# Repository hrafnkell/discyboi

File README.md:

# discyboi

**[discyboi.com](https://discyboi.com)** · [flight lab](https://discyboi.com/lab/)

A flight tracker that mounts on a disc golf disc and reports each throw over Bluetooth. The goal is enough sensor data for reliable flight prediction:

- release detection and release speed
- hyzer angle and nose angle
- spin rate
- wobble / off-axis torque

The hardware is a small round PCB built around an nRF54L15 BLE SoC and IMUs read over SPI. It runs from a CR2032 coin cell and mounts in a small screw-on case under the flight plate, or can be sealed (potted or conformal-coated) into the disc.

## Hardware

The current board is **[v4](v4/)**: Ø34 mm, a Fanstel BC15M module (nRF54L15, PCB antenna), and 2 × LSM6DSV320X (one at the centre, one at r = 9 mm). It runs from a CR2032 in a clip on the back, through an MCP1700 3.0 V regulator. The LiPo charger is on the board but not fitted (LIR2032 option). Gerbers and BOMs are in `v4/jlcpcb/`.

Each LSM6DSV320X has a ±320 g high-g accelerometer next to the IMU, and placing one 9 mm off-centre means spin rate can be computed from centripetal acceleration well past the gyro's 4000 dps limit. See the [v4 README](v4/README.md) for specs, the full pinout and how to regenerate the board.

Earlier revisions (v1: bare nRF54L15 + ADXL375, v2: Holyiot module, v3: the v4 design with a LiPo) were removed from the tree; they are in the git history.

## Layout

```
datasheets/            LSM6DSV320X IMU datasheet, TE/Linx coin-cell clip drawings (003 = CR2032, used on v4)
v4/                    KiCad project for the current board
v4/gen/                Python generators for v4's schematic, footprints and PCB (source of truth)
v4/jlcpcb/             fabrication outputs (gerbers, BOM, CPL)
v4/enclosure/          OpenSCAD case (base + screw-on battery lid), STLs, centring jig
firmware/              Zephyr firmware for the v4 board
web/                   discyboi.com: landing page, and the three.js flight lab (simulator, Web Bluetooth client, throw history)
```

## Tools

- KiCad 9 (schematic, PCB, `kicad-cli` for ERC/DRC and exports)
- Freerouting (`~/Downloads/freerouting*.AppImage`) for autorouting v4
- JLCPCB for fabrication. Mouser for the parts (single-supplier BOM)

## Firmware

[`firmware/`](firmware/) holds the Zephyr (v4.0) application for the v4 board. It runs on hardware (both IMUs, motion detection) and takes updates over Bluetooth through MCUboot; real throws are still to be checked. Its analysis maths passes host tests.

- **Detection:** finds throws with a pull/release state machine at 960 Hz, keeping a 3 s ring buffer.
- **Measurements:** release speed, hyzer, nose and launch angles, spin (from the gyro, or centripetal when the gyro saturates), wobble and flight time.
- **BLE:** sends each result, plus the battery level, and can send the raw capture for offline analysis.
- **Build:** `firmware/build.sh` runs the build in Docker. Flashing is over SWD (Tag-Connect), with logs over RTT.

See the [firmware README](firmware/README.md) for the BLE protocol and the bring-up TODO list.

## Web

[`web/`](web/) is a browser app (Vite + TypeScript + three.js, run with bun). It simulates disc flights from speed, spin, hyzer, nose and launch angle plus a disc's flight numbers, and animates them in 3D. It receives throws from the disc over Web Bluetooth (or from a fake disc with `?fake=1`) and keeps a throw history. It runs at [discyboi.com](https://discyboi.com): a landing page at `/` and the app under `/lab/`. See the [web README](web/README.md).

## Licence

Open source and open hardware: CERN-OHL-S-2.0 for the hardware, GPL-3.0 for the firmware, AGPL-3.0 for the web app, and CC-BY-SA-4.0 for the photos. Build your own freely; if you share or sell something based on it, credit this project and publish your changes under the same licence. The name "discyboi" is not included. See [LICENSE.md](LICENSE.md).

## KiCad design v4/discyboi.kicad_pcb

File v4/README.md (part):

# discyboi v4

Round 34 mm flight-tracker board that sits on a disc golf disc. It has a Fanstel BC15M (nRF54L15) BLE module and two LSM6DSV320X IMUs, and runs from a **CR2032 coin cell** in a clip on the back of the board.

v4 is v3 (now only in the git history) with the LiPo replaced by a replaceable coin cell, because small LiPo cells are hard to get shipped. The electronics, pinout and firmware are otherwise the same. The LiPo charger stays on the board but is **not fitted** (DNP). Fit it only if you use a rechargeable LIR2032.

| Top | Bottom (seen from below) |
|---|---|
|  |  |

## Specs

| | |
|---|---|
| MCU / radio | Fanstel **BC15M**: nRF54L15, BLE, PCB trace antenna. 6.0 × 9.6 mm, 36-pad LGA (6×6, 0.9 mm pitch) |
| IMU (centre) | **LSM6DSV320X** (U5): ±4000 dps gyro, ±16 g low-g accel and ±320 g high-g accel |
| IMU 2 (off-centre) | **LSM6DSV320X** (U3) at r = 9 mm, same orientation as U5 |
| Sensor bus | SPI (SPIM00, port 2), shared SCK/MOSI/MISO, one CS per IMU, two interrupt lines per IMU |
| Battery | **CR2032** in a TE/Linx **BAT-HLD-003-SMT** clip (BT1) on the bottom side. The cell's negative face sits on a Ø14 mm pad; the clip is the + contact |
| Bulk capacitor | C22 100 µF (1206) on VBAT, which supplies the radio's transmit bursts so the coin cell doesn't sag |
| Charger (**DNP**) | MCP73831-2 (U4) with R7 = 47 k (~21 mA), D2, R8, C13, D3 and R9 are not fitted. Fit them only for a rechargeable **LIR2032**. **Never fit them with a CR2032 in the clip** |
| Regulator | MCP1700-3002E LDO → **3.0 V** rail (+3V0) for everything |
| Battery sense | VBAT → 10 M / 10 M divider (+100 nF) → P1.06 / AIN2, so the ADC reads VBAT/2 (≈0.2 µA drain; sample slowly) |
| Charger detect | R9 (DNP) / R10 100 k → P1.03 (CHG_DET, NFC pad used as GPIO). With R9 unfitted, R10 holds it low |
| Debug | Tag-Connect TC2030-IDC-NL (no legs): SWD + reset. Logging over RTT |
| Status | Green LED on P2.09 (active high, 1 k) |
| PCB | 4 layers, Ø34 mm circle with a straight flat 10.2 mm above centre for the antenna. Finish: lead-free **HASL** (free, long shelf life), ENIG (flattest, costs extra) or OSP (flat, but short shelf life). See Ordering |

### Why two IMUs

The gyro saturates at 4000 dps, which is about **667 rpm**, and discs spin faster than that. U3 sits 9 mm from the centre, so it sees centripetal acceleration a = ω²r. Subtracting U5's reading, which sits at the centre and sees linear and gravity components only, leaves the spin term:

| Range used | Max a | Max spin at r = 9 mm |
|---|---|---|
| Gyro | – | ~667 rpm |
| Low-g accel ±16 g | 157 m/s² | ~1260 rpm |
| High-g accel ±320 g | 3140 m/s² | ~5600 rpm |

U5 at the centre also gives orientation (hyzer, nose angle, wobble) and release and impact detection.

## Pinout

### BC15M module (U1)

Only perimeter pads are used, so every signal escapes on the top layer with no vias under the module. Interrupts are on P0/P1 (GPIOTE30 / GPIOTE20). The SPI lines are on SPIM00's dedicated port-2 pins.

| Pad | nRF54L15 pin | Net | Function |
|---|---|---|---|
| F6 | VDD | +3V0 | Supply (C1 10 µF + C2 100 nF) |
| E1, F1 | GND | GND | |
| A3 | SWDIO | SWDIO | Debug |
| A4 | SWDCLK | SWDCLK | Debug |
| F3 | nRESET | NRESET | Debug / reset |
| C6 | P2.01 | SPI_SCK | SPIM00 SCK |
| D6 | P2.02 | SPI_MOSI | SPIM00 SDO |
| F5 | P2.04 | SPI_MISO | SPIM00 SDI |
| F2 | P2.06 | IMU_CS | U5 (centre IMU) chip select |
| A6 | P2.05 | ACC_CS | U3 (r = 9 mm IMU) chip select |
| A2 | P0.00 | IMU_INT1 | U5 INT1 |
| B1 | P1.08 | IMU_INT2 | U5 INT2 |
| A1 | P0.01 | ACC_INT1 | U3 INT1 |
| D1 | P1.12 | ACC_INT2 | U3 INT2 |
| B6 | P1.06 / AIN2 | VBAT_SENSE | Battery voltage ÷ 2 |
| A5 | P2.09 | LED | Green status LED (D1) via R5 |
| F4 | P1.03 (NFC1) | CHG_DET | Charger present (VCHG ÷ 2). Configure the NFC pads as GPIO |

All other pads are not connected.

### LSM6DSV320X (U5 centre, U3 off-centre)

SPI 4-wire mode. The analog hub / Qvar inputs are tied to GND and the aux SPI pins are left open (datasheet table 2, mode 1).

| Pin | Name | U5 net | U3 net |
|---|---|---|---|
| 1 | SDO/SA0 | SPI_MISO | SPI_MISO |
| 2 | SDx | GND | GND |
| 3 | SCx | GND | GND |
| 4 | INT1 | IMU_INT1 | ACC_INT1 |
| 5 | VDDIO | +3V0 | +3V0 |
| 6, 7 | GND | GND | GND |
| 8 | VDD | +3V0 | +3V0 |
| 9 | INT2 | IMU_INT2 | ACC_INT2 |
| 10 | OCS_Aux | NC | NC |
| 11 | SDO_Aux | NC | NC |
| 12 | CS | IMU_CS | ACC_CS |
| 13 | SCL/SPC | SPI_SCK | SPI_SCK |
| 14 | SDA/SDI | SPI_MOSI | SPI_MOSI |

Decoupling: U5 has C10/C12 100 nF and C11 1 µF. U3 has C19/C20 100 nF and C21 1 µF.

### SWD: Tag-Connect TC2030 (J2)

| Pin | Signal |
|---|---|
| 1 | +3V0 (VTref) |
| 2 | SWDIO |
| 3 | NRESET |
| 4 | SWDCLK |
| 5 | GND |
| 6 | NC |

The footprint is the no-legs version, so use a TC2030-CTX-NL cable with the retaining clip. J2 sits at the top left so the cable's guide pins, which poke through the board, clear the coin cell on the back. Or solder thin wires to the pads for bring-up.

### Pads

| Pad | Net | |
|---|---|---|
| TP1 | VBAT | BAT+ (bench supply / measuring) |
| TP2 | GND | BAT− |
| TP3 | VCHG | CHG+ (5 V in, LIR2032 build only) |
| TP4 | GND | CHG− |

All four pads are 2 × 2 mm, along the bottom edge of the top side. With a CR2032 build, don't connect anything to CHG+.

## Power path

```
BT1 CR2032 (clip, bottom) ── VBAT ── C22 100 µF, C14 4.7 µF
                              │   └─ R3/R4 10M:10M ─► VBAT_SENSE (P1.06)
                              ▼
                     MCP1700 3.0 V (U2, C16 in / C17 out) ──► +3V0

(DNP, LIR2032 only)  CHG+ 5V ──D3──C13──► MCP73831 (U4, 21 mA) ──► VBAT
```

A fresh CR2032 is about 3.0 V, so the MCP1700 is in dropout and the rail simply follows the cell (≈2.6–3.0 V for most of its life). The nRF54L15 and both IMUs run down to about 1.7–1.8 V, so the cell can be used almost to empty.

**Runtime (estimate).** About 1.7–2 mA while armed (both IMUs at 960 Hz plus the CPU) and 11 µA in deep sleep. A CR2032 gives roughly 150–180 mAh at that load, so about 35–40 rounds of two hours armed time. Cold weather reduces this. The radio's 5–10 mA transmit bursts come mostly from C22.

**Battery level.** The firmware detects the battery type (`CONFIG_DISCY_BATTERY_AUTO`, default): coin-cell curve (3.0 V = 100 %, 2.0 V = 0 %) until VBAT is seen above 3.45 V, then the LiPo curve.

## LiPo build (same board)

The same board can run from a 1S LiPo instead of the coin cell, for example a 20 × 20 × 4.5 mm, 150 mAh pouch.

**Each board is either a coin-cell build or a LiPo build, never both.** A LiPo or a 5 V charger connected to a primary CR2032 forces current into it, and that can make the cell leak, swell or catch fire. On a LiPo board, leave the clip off.

| | Coin-cell build | LiPo build |
|---|---|---|
| BT1 clip | Fitted | **Not fitted** |
| Battery | CR2032 in the clip | LiPo leads: + to a clip tab pad (or TP1 BAT+), − to the round pad's edge (or TP2 BAT−) |
| U4, R8, D2, C13, D3, R9 | Not fitted | Fitted |
| R7 (charge current = 1000 V / R7) | Not fitted | **10 k = 100 mA** for 150 mAh (≈0.7C) |
| Charging | – | 5 V on CHG+ / CHG− (TP3 / TP4). The red LED is lit while charging |
| CHG_DET (P1.03) | Held low by R10 | High while a charger is connected |

Notes for the LiPo build:
- **Use a protected cell.** It needs a protection PCB on the tabs for over-discharge and short-circuit. Small pouch cells often have it, which makes them a couple of mm longer than the nominal size.
- **Insulate the cell from the board.** Put a layer of Kapton tape over the bottom of the board before you stick the cell there, so the pouch can't rub through to the exposed round pad or the vias.
- **Placement:** the 20 × 20 mm cell fits on the bottom in the same place as the coin cell, centred 2.5 mm below the board centre, so balance and antenna clearance stay the same.
- **Regulator:** the LDO now regulates properly to 3.0 V. Nothing else on the board changes.
- **Same firmware:** it switches to the LiPo battery curve on its own once VBAT is above 3.45 V.

## PCB

- **Stackup:** F.Cu signals plus GND pour, In1 solid GND, In2 solid +3V0, B.Cu GND pour. GND stitching vias run around the rim.
- **Rules:** 0.12 mm clearance. Tracks are 0.15 mm signal, 0.25 mm +3V0/GND and 0.3 mm VBAT/VCHG. Vias are 0.45 / 0.2 mm (JLC charges for a 4-wire Kelvin test on 0.4 / 0.2 mm vias), with 0.25 mm copper-to-edge clearance.
- **Antenna:** the module is placed so that its shield/antenna boundary sits on the board flat. The 3.6 mm trace antenna overhangs the edge with no copper under it. Vias are kept out from under the module.
- **Coin cell:** the cell centre is 2.5 mm below the board centre, which keeps it more than 2 mm from the antenna edge and partly balances the module at the top. The clip's open end faces the module and the cell slides in from that side.
  - The negative pad is Ø14 mm instead of the 17.9 mm in TE's drawing. A CR2032's flat negative face is wider than that, and the smaller pad leaves a ring of bottom-layer routing under the cell. Those traces stay under solder mask.
  - The pad has GND vias in it. That's fine for a pressure contact.
- **Mass:** the cell is about 3 g. Check the disc's balance with the cell fitted before potting or gluing.

## Ordering

- **JLCPCB (PCB):** upload `jlcpcb/discyboi-gerbers.zip`.
  - 4 layers, **1.0 mm** thick (the enclosure STLs assume 1.0 mm). Use a **0.10 mm** top-side stencil.
  - Surface finish:
    - **Lead-free HASL** (free) suits boards that may sit in a drawer, because it stays solderable for a year or more. The battery's negative pad comes solder-coated, so it needs no treatment unless it's visibly lumpy; then flatten it with the iron and solder wick. HASL pads are slightly domed, so take a little extra care with the 0.5 mm-pitch IMUs: use the 0.10 mm stencil, press each IMU down level after placing it, and inspect after reflow.
    - **ENIG** costs extra. It's the flattest finish and has a long shelf life. The battery pad needs nothing.
    - **OSP** (free) is flat, but assemble within a few months. Tin the battery pad after reflow (flux and solder, then wick it thin and flat), because bare copper oxidises.
  - Order a **top-side** stencil only, 0.10 mm thick.
  - The stencil also has apertures for the unfitted charger pads. The paste just tins those pads, which is harmless and handy if you fit the charger later.
- **JLC assembly (optional):** `jlcpcb/discyboi-BOM.csv` + `discyboi-CPL.csv` cover all fitted top-side parts, the BC15M included. Unfitted parts and the battery clip are left out.
  - **The BC15M, the LSM6DSV320X and the 10 M resistors have no LCSC code.** Get them through JLCPCB's Global Sourcing (from Mouser / DigiKey) or send them as consigned parts. The BC15M is an LGA: ask for X-ray inspection.
- **Generic passives:** the caps, resistors and LED can be any brand that meets the spec in the Mouser BOM's Substitute column (the MPNs are examples). Mind the 100 µF (6.3 V or more, X5R) and the LED (yellow-green AlInGaP, Vf ≈ 2 V: an InGaN "true green" barely lights from 3 V through 1 k). U1, U2, U3/U5 and BT1 must be the exact parts.
- **Mouser:** `discyboi-mouser-BOM.csv` lists every fitted part with its MPN, including the BC15M (Mouser 308-BC15M) and the BAT-HLD-003-SMT clip. Not in any BOM: the CR2032 itself, and for the case 3 × M2 × 6 mm countersunk screws and VHB tape.
  - For a rechargeable build, also buy U4 MCP73831T-2ACI/OT, R8 1 k, D2 (LTST-C191KRKT), C13 4.7 µF, D3 ESD5Z5.0T1G and R9 100 k.
  - R7 depends on the cell: 10 k (RC0402FR-0710KL, 100 mA) for a 150 mAh LiPo, or 47 k (RC0402FR-0747KL, 21 mA) for a LIR2032.
- **Assembly order:**
  1. Paste and reflow the top side (BC15M, IMUs and passives).
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
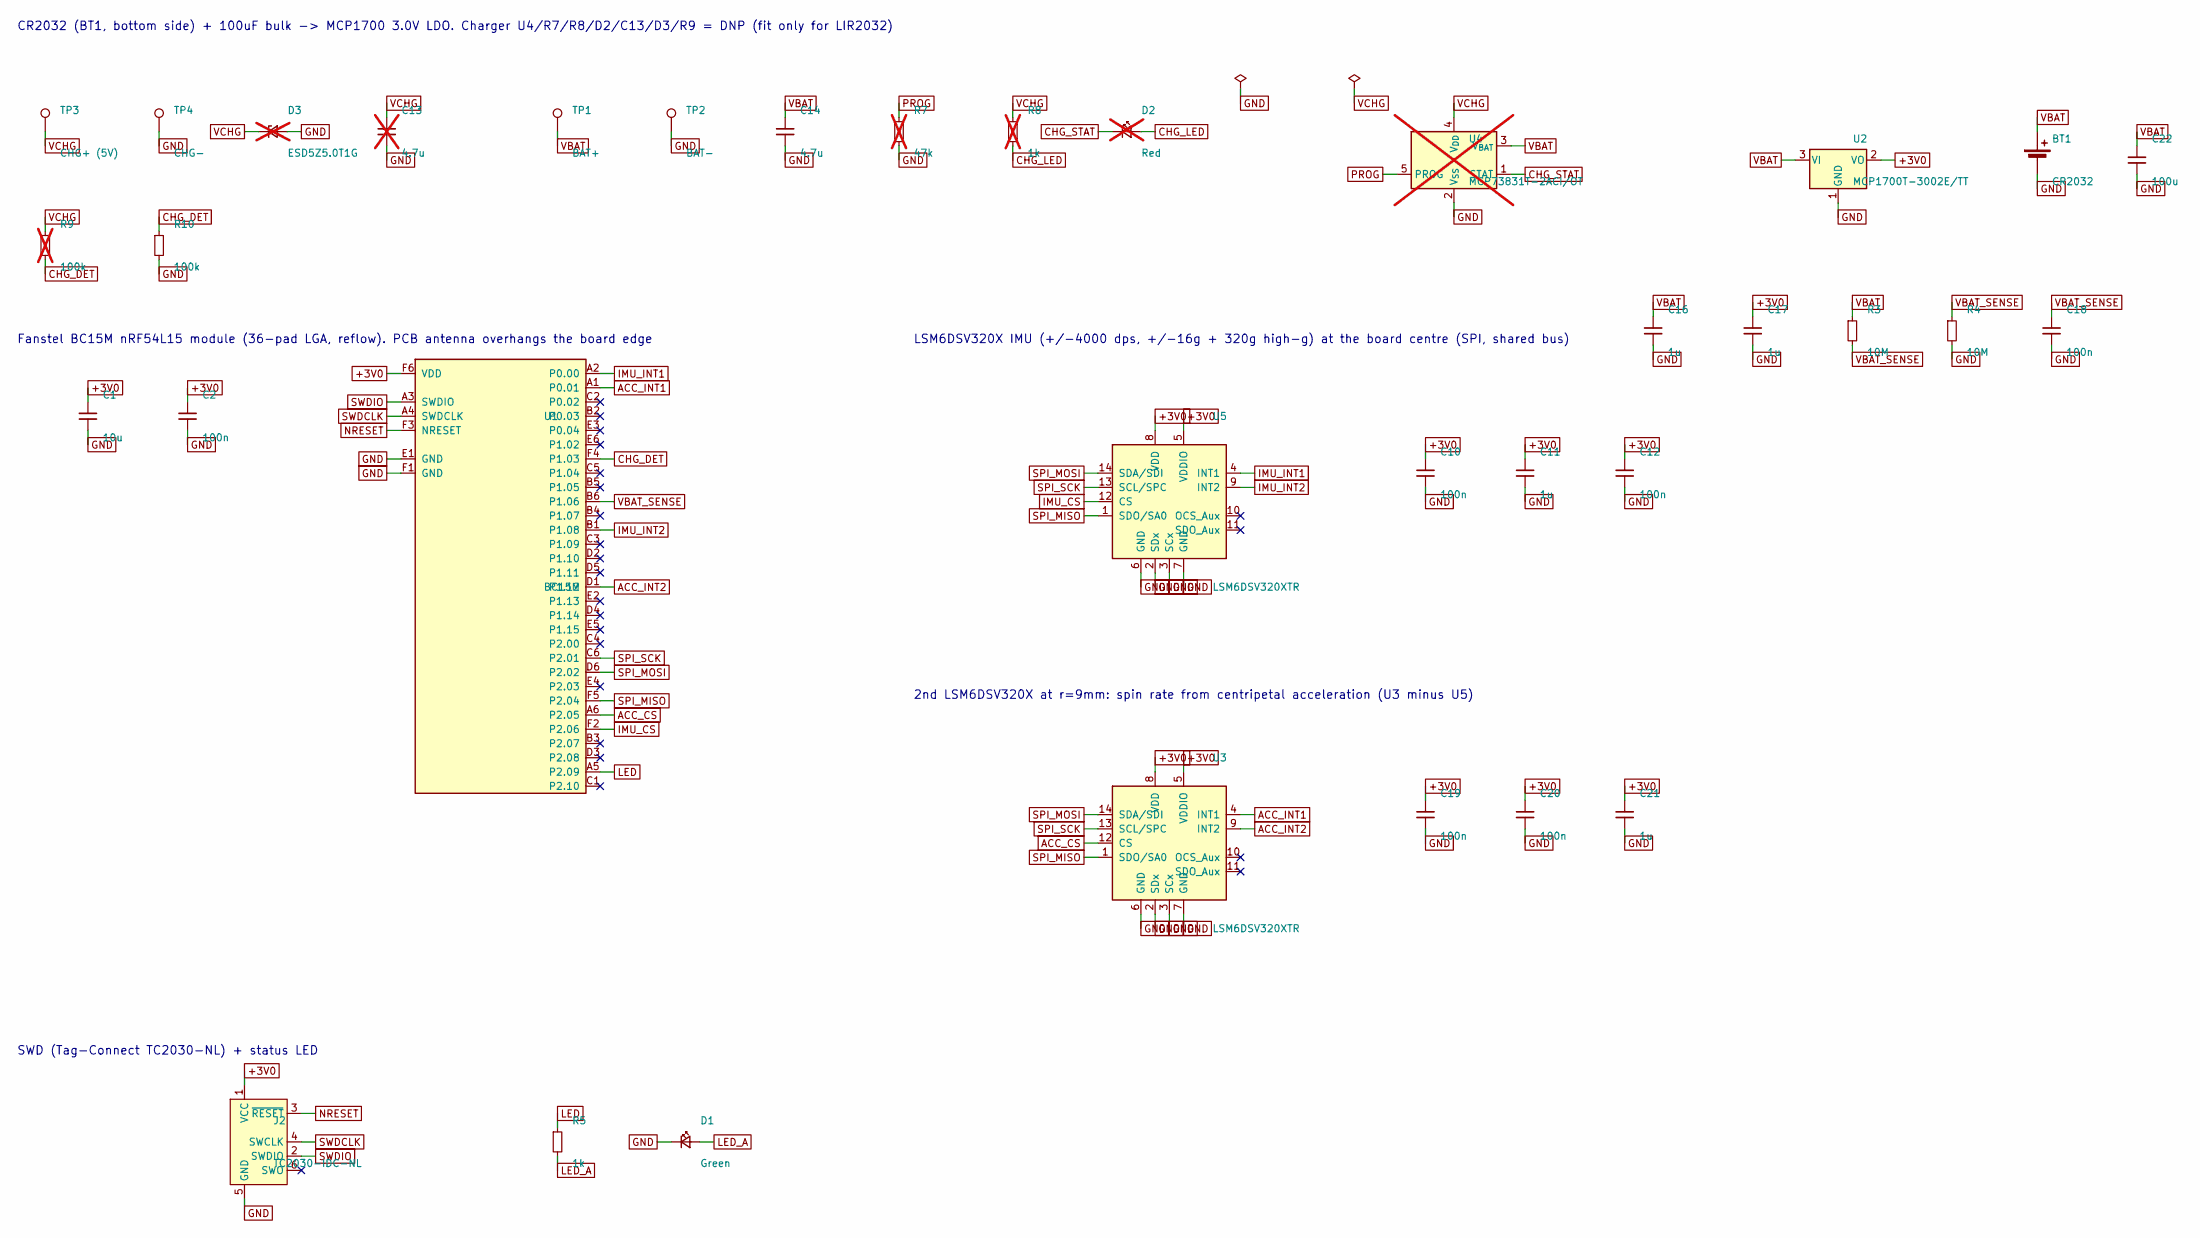
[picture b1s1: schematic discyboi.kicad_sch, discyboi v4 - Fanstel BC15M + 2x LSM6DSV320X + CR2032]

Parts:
BT1: CR2032; Linx_BAT-HLD-003-SMT; MPN BAT-HLD-003-SMT
C1: 10u; C_0402_1005Metric; MPN CL05A106MQ5NUNC; LCSC C15525
C2, C10, C12, C18, C19, C20: 100n; C_0402_1005Metric; MPN CL05B104KO5NNNC; LCSC C1525
C11, C16, C17, C21: 1u; C_0402_1005Metric; MPN CL05A105KA5NQNC; LCSC C52923
C13: 4.7u; C_0402_1005Metric; MPN CL05A475MP5NRNC; LCSC C23733; not fitted
C14: 4.7u; C_0402_1005Metric; MPN CL05A475MP5NRNC; LCSC C23733
C22: 100u; C_1206_3216Metric; MPN CL31A107MQHNNNE; LCSC C15008
D1: Green; LED_0603_1608Metric; MPN LTST-C191KGKT; LCSC C72043
D2: Red; LED_0603_1608Metric; MPN LTST-C191KRKT; LCSC C2286; not fitted
D3: ESD5Z5.0T1G; D_SOD-523; MPN ESD5Z5.0T1G; LCSC C82044; not fitted
J2: TC2030-IDC-NL; Tag-Connect_TC2030-IDC-NL_2x03_P1.27mm_Vertical
R3, R4: 10M; R_0402_1005Metric; MPN RC0402FR-0710ML
R5: 1k; R_0402_1005Metric; MPN RC0402FR-071KL; LCSC C11702
R7: 47k; R_0402_1005Metric; MPN RC0402FR-0747KL; LCSC C25819; not fitted
R8: 1k; R_0402_1005Metric; MPN RC0402FR-071KL; LCSC C11702; not fitted
R9: 100k; R_0402_1005Metric; MPN RC0402FR-07100KL; LCSC C25741; not fitted
R10: 100k; R_0402_1005Metric; MPN RC0402FR-07100KL; LCSC C25741
TP1: BAT+; TestPoint_Pad_2.0x2.0mm
TP2: BAT-; TestPoint_Pad_2.0x2.0mm
TP3: CHG+ (5V); TestPoint_Pad_2.0x2.0mm
TP4: CHG-; TestPoint_Pad_2.0x2.0mm
U1: BC15M; Fanstel_BC15M; MPN BC15M
U2: MCP1700T-3002E/TT; SOT-23; MPN MCP1700T-3002E/TT; LCSC C62244
U3, U5: LSM6DSV320XTR; LGA-14_3x2.5mm_P0.5mm_LayoutBorder3x4y; MPN LSM6DSV320XTR
U4: MCP73831T-2ACI/OT; SOT-23-5; MPN MCP73831T-2ACI/OT; LCSC C424093; not fitted

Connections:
+3V0: C1.1, C2.1, C10.1, C11.1, C12.1, C17.1, C19.1, C20.1, C21.1, J2.1 (VCC), U1.F6 (VDD), U2.2 (VO), U3.5 (VDDIO), U3.8 (VDD), U5.5 (VDDIO), U5.8 (VDD)
ACC_CS: U1.A6 (P2.05), U3.12 (CS)
ACC_INT1: U1.A1 (P0.01), U3.4 (INT1)
ACC_INT2: U1.D1 (P1.12), U3.9 (INT2)
CHG_DET: R9.2, R10.1, U1.F4 (P1.03)
CHG_LED: D2.2 (A), R8.2
CHG_STAT: D2.1 (K), U4.1 (STAT)
GND: BT1.2 (-), C1.2, C2.2, C10.2, C11.2, C12.2, C13.2, C14.2, C16.2, C17.2, C18.2, C19.2, C20.2, C21.2, C22.2, D1.1 (K), D3.2 (A), J2.5 (GND), R4.2, R7.2, R10.2, TP2.1, TP4.1, U1.E1 (GND), U1.F1 (GND), U2.1 (GND), U3.2 (SDx), U3.3 (SCx), U3.6 (GND), U3.7 (GND), U4.2 (V_{SS}), U5.2 (SDx), U5.3 (SCx), U5.6 (GND), U5.7 (GND)
IMU_CS: U1.F2 (P2.06), U5.12 (CS)
IMU_INT1: U1.A2 (P0.00), U5.4 (INT1)
IMU_INT2: U1.B1 (P1.08), U5.9 (INT2)
LED: R5.1, U1.A5 (P2.09)
LED_A: D1.2 (A), R5.2
NRESET: J2.3 (~RESET), U1.F3 (NRESET)
PROG: R7.1, U4.5 (PROG)
SPI_MISO: U1.F5 (P2.04), U3.1 (SDO/SA0), U5.1 (SDO/SA0)
SPI_MOSI: U1.D6 (P2.02), U3.14 (SDA/SDI), U5.14 (SDA/SDI)
SPI_SCK: U1.C6 (P2.01), U3.13 (SCL/SPC), U5.13 (SCL/SPC)
SWDCLK: J2.4 (SWCLK), U1.A4 (SWDCLK)
SWDIO: J2.2 (SWDIO), U1.A3 (SWDIO)
VBAT: BT1.1 (+), C14.1, C16.1, C22.1, R3.1, TP1.1, U2.3 (VI), U4.3 (V_{BAT})
VBAT_SENSE: C18.1, R3.2, R4.1, U1.B6 (P1.06)
VCHG: C13.1, D3.1 (K), R8.1, R9.1, TP3.1, U4.4 (V_{DD})

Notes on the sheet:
CR2032 (BT1, bottom side) + 100uF bulk -> MCP1700 3.0V LDO. Charger U4/R7/R8/D2/C13/D3/R9 = DNP (fit only for LIR2032)
Fanstel BC15M nRF54L15 module (36-pad LGA, reflow). PCB antenna overhangs the board edge
LSM6DSV320X IMU (+/-4000 dps, +/-16g + 320g high-g) at the board centre (SPI, shared bus)
2nd LSM6DSV320X at r=9mm: spin rate from centripetal acceleration (U3 minus U5)
SWD (Tag-Connect TC2030-NL) + status LED

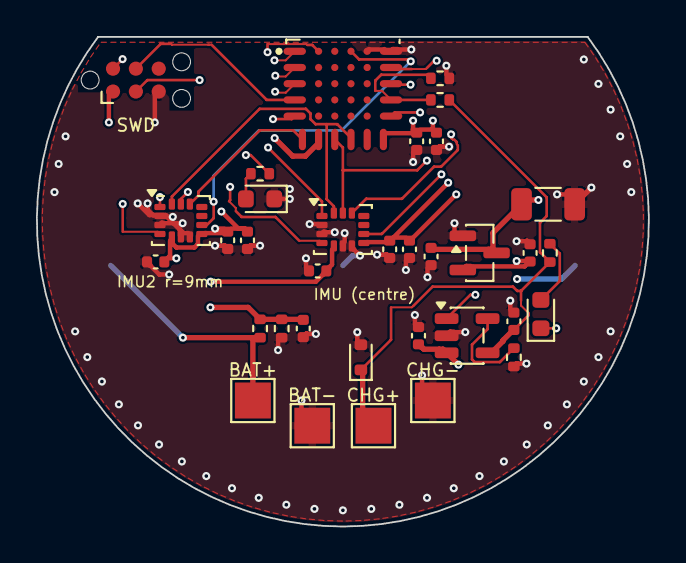
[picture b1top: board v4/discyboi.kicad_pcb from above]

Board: 4 copper layers, 34.0 x 27.2 mm, 35 parts (1 on the bottom side), 23 nets.

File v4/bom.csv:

"Ref","Value","Footprint","LCSC","MPN","Manufacturer","Qty"
"BT1","CR2032","discyboi:Linx_BAT-HLD-003-SMT","","BAT-HLD-003-SMT","TE Connectivity Linx","1"
"C1","10u","Capacitor_SMD:C_0402_1005Metric","C15525","CL05A106MQ5NUNC","Samsung","1"
"C2,C10,C12,C18-C20","100n","Capacitor_SMD:C_0402_1005Metric","C1525","CL05B104KO5NNNC","Samsung","6"
"C11,C16,C17,C21","1u","Capacitor_SMD:C_0402_1005Metric","C52923","CL05A105KA5NQNC","Samsung","4"
"C14","4.7u","Capacitor_SMD:C_0402_1005Metric","C23733","CL05A475MP5NRNC","Samsung","1"
"C22","100u","Capacitor_SMD:C_1206_3216Metric","C15008","CL31A107MQHNNNE","Samsung","1"
"D1","Green","LED_SMD:LED_0603_1608Metric","C72043","LTST-C191KGKT","Lite-On","1"
"R3,R4","10M","Resistor_SMD:R_0402_1005Metric","","RC0402FR-0710ML","Yageo","2"
"R5","1k","Resistor_SMD:R_0402_1005Metric","C11702","RC0402FR-071KL","Yageo","1"
"R10","100k","Resistor_SMD:R_0402_1005Metric","C25741","RC0402FR-07100KL","Yageo","1"
"U1","BC15M","discyboi:Fanstel_BC15M","","BC15M","Fanstel","1"
"U2","MCP1700T-3002E/TT","Package_TO_SOT_SMD:SOT-23","C62244","MCP1700T-3002E/TT","Microchip","1"
"U3,U5","LSM6DSV320XTR","Package_LGA:LGA-14_3x2.5mm_P0.5mm_LayoutBorder3x4y","","LSM6DSV320XTR","STMicroelectronics","2"

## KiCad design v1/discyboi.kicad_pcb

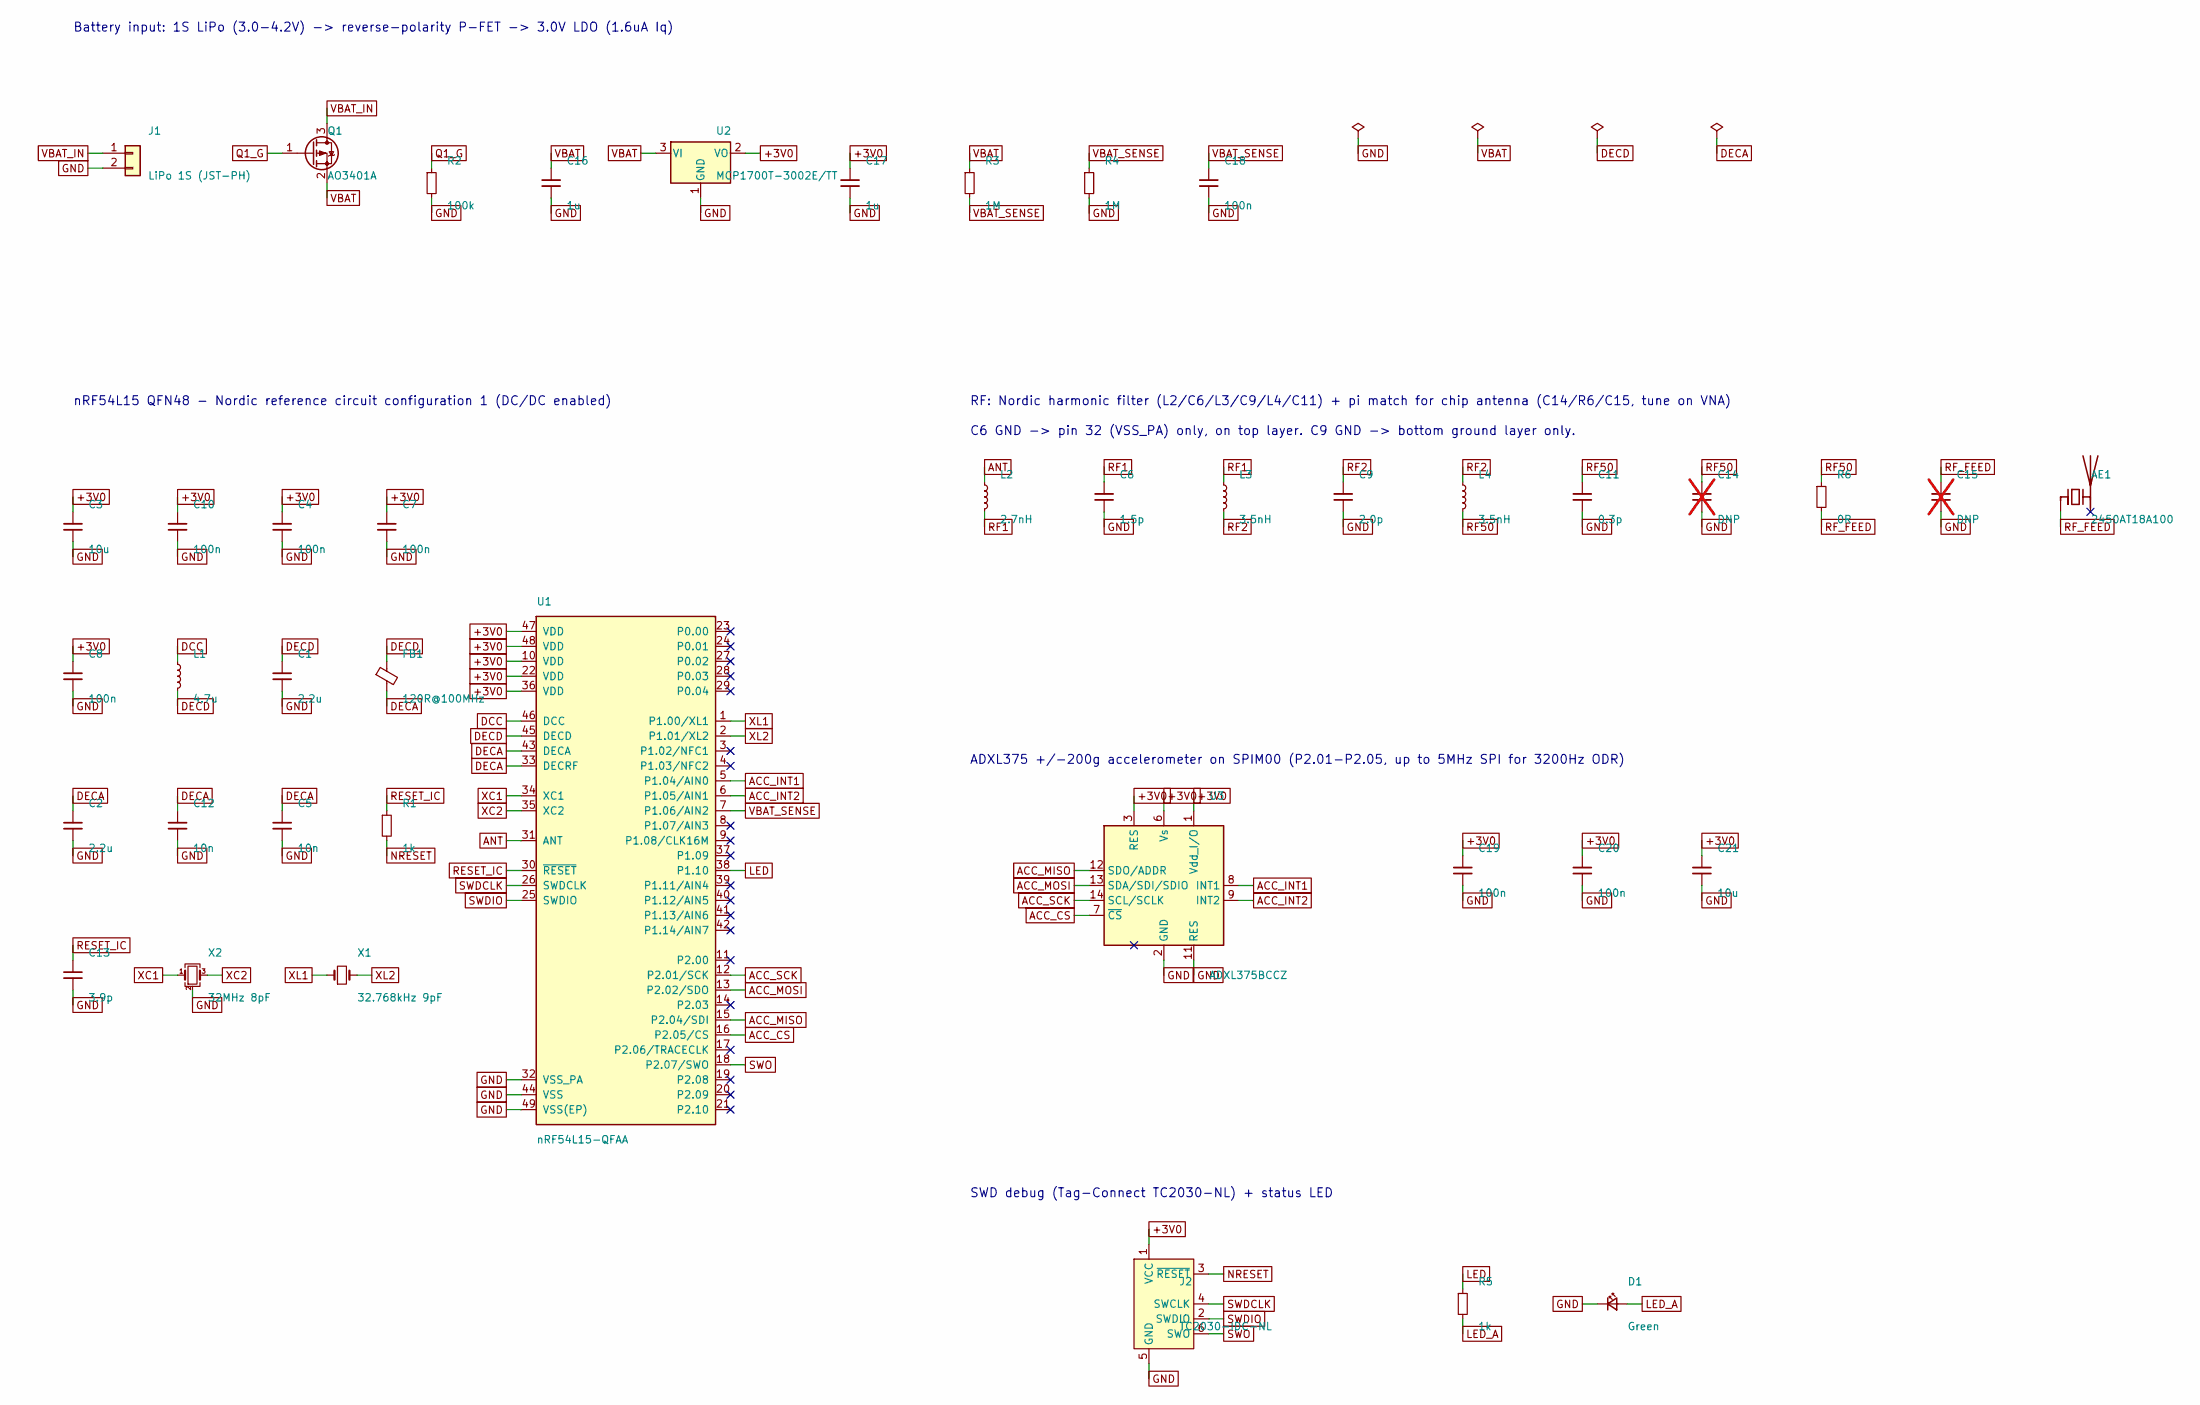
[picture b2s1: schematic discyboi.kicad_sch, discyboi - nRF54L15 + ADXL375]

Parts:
AE1: 2450AT18A100; Johanson_2450AT18x100; MPN 2450AT18A100E
C1, C2: 2.2u; C_0201_0603Metric
C3, C21: 10u; C_0402_1005Metric
C4, C7, C8, C10: 100n; C_0201_0603Metric
C5, C12: 10n; C_0201_0603Metric
C6: 1.5p; C_0201_0603Metric; MPN GJM0335C1E1R5WB01
C9: 2.0p; C_0201_0603Metric; MPN GJM0335C1E2R0WB01
C11: 0.3p; C_0201_0603Metric
C13: 3.9p; C_0201_0603Metric
C14, C15: DNP; C_0201_0603Metric; not fitted
C16, C17: 1u; C_0402_1005Metric
C18, C19, C20: 100n; C_0402_1005Metric
D1: Green; LED_0402_1005Metric
FB1: 120R@100MHz; L_0201_0603Metric
J1: LiPo 1S (JST-PH); JST_PH_S2B-PH-SM4-TB_1x02-1MP_P2.00mm_Horizontal; MPN S2B-PH-SM4-TB
J2: TC2030-IDC-NL; Tag-Connect_TC2030-IDC-NL_2x03_P1.27mm_Vertical
L1: 4.7u; L_0603_1608Metric
L2: 2.7nH; L_0201_0603Metric; MPN LQP03HQ2N7B02
L3, L4: 3.5nH; L_0201_0603Metric; MPN LQP03HQ3N5B02
Q1: AO3401A; SOT-23; MPN AO3401A
R1: 1k; R_0201_0603Metric
R2: 100k; R_0402_1005Metric
R3, R4: 1M; R_0402_1005Metric
R5: 1k; R_0402_1005Metric
R6: 0R; R_0201_0603Metric
U1: nRF54L15-QFAA; QFN-48-1EP_6x6mm_P0.4mm_EP4.6x4.6mm_ThermalVias; MPN NRF54L15-QFAA-R
U2: MCP1700T-3002E/TT; SOT-23; MPN MCP1700T-3002E/TT
U3: ADXL375BCCZ; LGA-14_3x5mm_P0.8mm_LayoutBorder1x6y; MPN ADXL375BCCZ
X1: 32.768kHz 9pF; Crystal_SMD_2012-2Pin_2.0x1.2mm
X2: 32MHz 8pF; Crystal_SMD_2016-4Pin_2.0x1.6mm

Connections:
+3V0: C3.1, C4.1, C7.1, C8.1, C10.1, C17.1, C19.1, C20.1, C21.1, J2.1 (VCC), U1.10 (VDD), U1.22 (VDD), U1.36 (VDD), U1.47 (VDD), U1.48 (VDD), U2.2 (VO), U3.1 (Vdd_I/O), U3.3 (RES), U3.6 (Vs)
ACC_CS: U1.16 (P2.05/CS), U3.7 (~CS)
ACC_INT1: U1.5 (P1.04/AIN0), U3.8 (INT1)
ACC_INT2: U1.6 (P1.05/AIN1), U3.9 (INT2)
ACC_MISO: U1.15 (P2.04/SDI), U3.12 (SDO/ADDR)
ACC_MOSI: U1.13 (P2.02/SDO), U3.13 (SDA/SDI/SDIO)
ACC_SCK: U1.12 (P2.01/SCK), U3.14 (SCL/SCLK)
ANT: L2.1, U1.31 (ANT)
DCC: L1.1, U1.46 (DCC)
DECA: C2.1, C5.1, C12.1, FB1.2, U1.33 (DECRF), U1.43 (DECA)
DECD: C1.1, FB1.1, L1.2, U1.45 (DECD)
GND: C1.2, C2.2, C3.2, C4.2, C5.2, C6.2, C7.2, C8.2, C9.2, C10.2, C11.2, C12.2, C13.2, C14.2, C15.2, C16.2, C17.2, C18.2, C19.2, C20.2, C21.2, D1.1 (K), J1.2, J2.5 (GND), R2.2, R4.2, U1.32 (VSS_PA), U1.44 (VSS), U1.49 (VSS(EP)), U2.1 (GND), U3.2 (GND), U3.4 (GND), U3.5 (GND), U3.11 (RES), X2.2 (G), X2.4 (G)
LED: R5.1, U1.38 (P1.10)
LED_A: D1.2 (A), R5.2
NRESET: J2.3 (~RESET), R1.2
Q1_G: Q1.1 (G), R2.1
RESET_IC: C13.1, R1.1, U1.30 (~RESET)
RF1: C6.1, L2.2, L3.1
RF2: C9.1, L3.2, L4.1
RF50: C11.1, C14.1, L4.2, R6.1
RF_FEED: AE1.1 (FEED), C15.1, R6.2
SWDCLK: J2.4 (SWCLK), U1.26 (SWDCLK)
SWDIO: J2.2 (SWDIO), U1.25 (SWDIO)
SWO: J2.6 (SWO), U1.18 (P2.07/SWO)
VBAT: C16.1, Q1.2 (S), R3.1, U2.3 (VI)
VBAT_IN: J1.1, Q1.3 (D)
VBAT_SENSE: C18.1, R3.2, R4.1, U1.7 (P1.06/AIN2)
XC1: U1.34 (XC1), X2.1
XC2: U1.35 (XC2), X2.3
XL1: U1.1 (P1.00/XL1), X1.1
XL2: U1.2 (P1.01/XL2), X1.2

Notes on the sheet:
Battery input: 1S LiPo (3.0-4.2V) -> reverse-polarity P-FET -> 3.0V LDO (1.6uA Iq)
nRF54L15 QFN48 - Nordic reference circuit configuration 1 (DC/DC enabled)
RF: Nordic harmonic filter (L2/C6/L3/C9/L4/C11) + pi match for chip antenna (C14/R6/C15, tune on VNA)
C6 GND -> pin 32 (VSS_PA) only, on top layer. C9 GND -> bottom ground layer only.
ADXL375 +/-200g accelerometer on SPIM00 (P2.01-P2.05, up to 5MHz SPI for 3200Hz ODR)
SWD debug (Tag-Connect TC2030-NL) + status LED

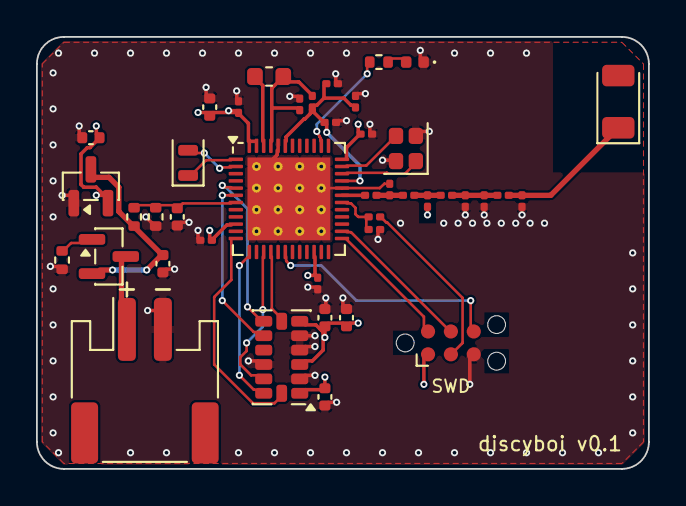
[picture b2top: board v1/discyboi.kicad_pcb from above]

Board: 4 copper layers, 34.0 x 24.0 mm, 42 parts (0 on the bottom side), 31 nets.

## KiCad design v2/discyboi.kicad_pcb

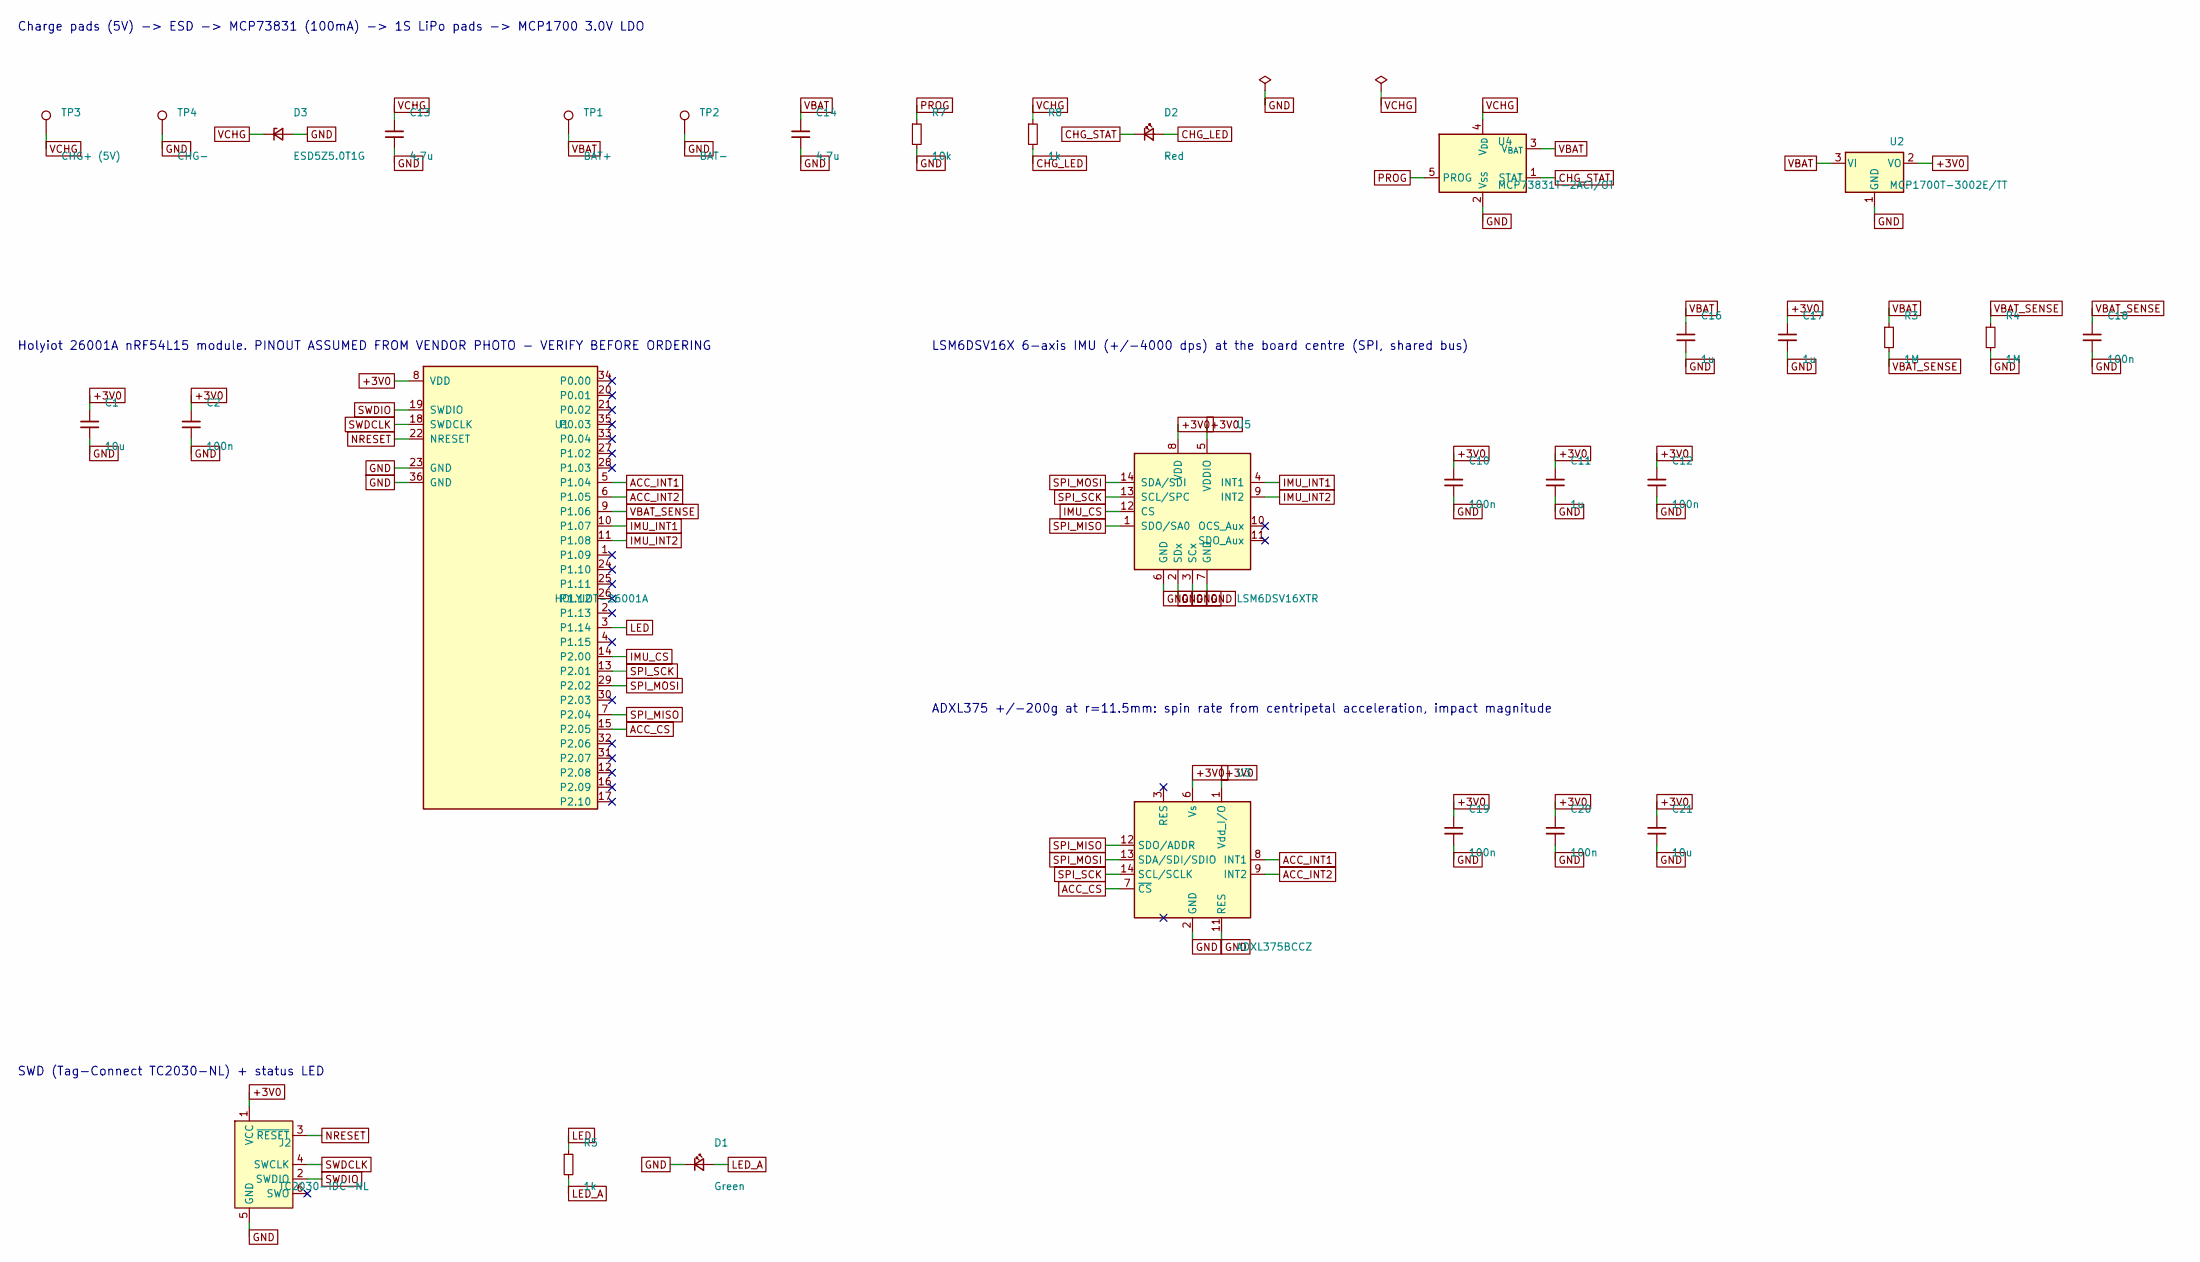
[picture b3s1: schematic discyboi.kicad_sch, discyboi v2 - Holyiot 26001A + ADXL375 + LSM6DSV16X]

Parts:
C1, C21: 10u; C_0402_1005Metric; MPN CL05A106MQ5NUNC; LCSC C15525
C2, C10, C12, C18, C19, C20: 100n; C_0402_1005Metric; MPN CL05B104KO5NNNC; LCSC C1525
C11, C16, C17: 1u; C_0402_1005Metric; MPN CL05A105KA5NQNC; LCSC C52923
C13, C14: 4.7u; C_0402_1005Metric; MPN CL05A475MP5NRNC; LCSC C23733
D1: Green; LED_0603_1608Metric; MPN LTST-C191KGKT; LCSC C72043
D2: Red; LED_0603_1608Metric; MPN LTST-C191KRKT; LCSC C2286
D3: ESD5Z5.0T1G; D_SOD-523; MPN ESD5Z5.0T1G; LCSC C82044
J2: TC2030-IDC-NL; Tag-Connect_TC2030-IDC-NL_2x03_P1.27mm_Vertical
R3, R4: 1M; R_0402_1005Metric; MPN RC0402FR-071ML; LCSC C26083
R5, R8: 1k; R_0402_1005Metric; MPN RC0402FR-071KL; LCSC C11702
R7: 10k; R_0402_1005Metric; MPN RC0402FR-0710KL; LCSC C25744
TP1: BAT+; TestPoint_Pad_2.0x2.0mm
TP2: BAT-; TestPoint_Pad_2.0x2.0mm
TP3: CHG+ (5V); TestPoint_Pad_2.0x2.0mm
TP4: CHG-; TestPoint_Pad_2.0x2.0mm
U1: HOLYIOT-26001A; Holyiot_26001A; MPN HOLYIOT-26001A
U2: MCP1700T-3002E/TT; SOT-23; MPN MCP1700T-3002E/TT; LCSC C62244
U3: ADXL375BCCZ; LGA-14_3x5mm_P0.8mm_LayoutBorder1x6y; MPN ADXL375BCCZ-RL7; LCSC C579466
U4: MCP73831T-2ACI/OT; SOT-23-5; MPN MCP73831T-2ACI/OT; LCSC C424093
U5: LSM6DSV16XTR; LGA-14_3x2.5mm_P0.5mm_LayoutBorder3x4y; MPN LSM6DSV16XTR; LCSC C5267406

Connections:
+3V0: C1.1, C2.1, C10.1, C11.1, C12.1, C17.1, C19.1, C20.1, C21.1, J2.1 (VCC), U1.8 (VDD), U2.2 (VO), U3.1 (Vdd_I/O), U3.6 (Vs), U5.5 (VDDIO), U5.8 (VDD)
ACC_CS: U1.15 (P2.05), U3.7 (~CS)
ACC_INT1: U1.5 (P1.04), U3.8 (INT1)
ACC_INT2: U1.6 (P1.05), U3.9 (INT2)
CHG_LED: D2.2 (A), R8.2
CHG_STAT: D2.1 (K), U4.1 (STAT)
GND: C1.2, C2.2, C10.2, C11.2, C12.2, C13.2, C14.2, C16.2, C17.2, C18.2, C19.2, C20.2, C21.2, D1.1 (K), D3.2 (A), J2.5 (GND), R4.2, R7.2, TP2.1, TP4.1, U1.23 (GND), U1.36 (GND), U2.1 (GND), U3.2 (GND), U3.4 (GND), U3.5 (GND), U3.11 (RES), U4.2 (V_{SS}), U5.2 (SDx), U5.3 (SCx), U5.6 (GND), U5.7 (GND)
IMU_CS: U1.14 (P2.00), U5.12 (CS)
IMU_INT1: U1.10 (P1.07), U5.4 (INT1)
IMU_INT2: U1.11 (P1.08), U5.9 (INT2)
LED: R5.1, U1.3 (P1.14)
LED_A: D1.2 (A), R5.2
NRESET: J2.3 (~RESET), U1.22 (NRESET)
PROG: R7.1, U4.5 (PROG)
SPI_MISO: U1.7 (P2.04), U3.12 (SDO/ADDR), U5.1 (SDO/SA0)
SPI_MOSI: U1.29 (P2.02), U3.13 (SDA/SDI/SDIO), U5.14 (SDA/SDI)
SPI_SCK: U1.13 (P2.01), U3.14 (SCL/SCLK), U5.13 (SCL/SPC)
SWDCLK: J2.4 (SWCLK), U1.18 (SWDCLK)
SWDIO: J2.2 (SWDIO), U1.19 (SWDIO)
VBAT: C14.1, C16.1, R3.1, TP1.1, U2.3 (VI), U4.3 (V_{BAT})
VBAT_SENSE: C18.1, R3.2, R4.1, U1.9 (P1.06)
VCHG: C13.1, D3.1 (K), R8.1, TP3.1, U4.4 (V_{DD})

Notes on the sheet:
Charge pads (5V) -> ESD -> MCP73831 (100mA) -> 1S LiPo pads -> MCP1700 3.0V LDO
Holyiot 26001A nRF54L15 module. PINOUT ASSUMED FROM VENDOR PHOTO - VERIFY BEFORE ORDERING
LSM6DSV16X 6-axis IMU (+/-4000 dps) at the board centre (SPI, shared bus)
ADXL375 +/-200g at r=11.5mm: spin rate from centripetal acceleration, impact magnitude
SWD (Tag-Connect TC2030-NL) + status LED

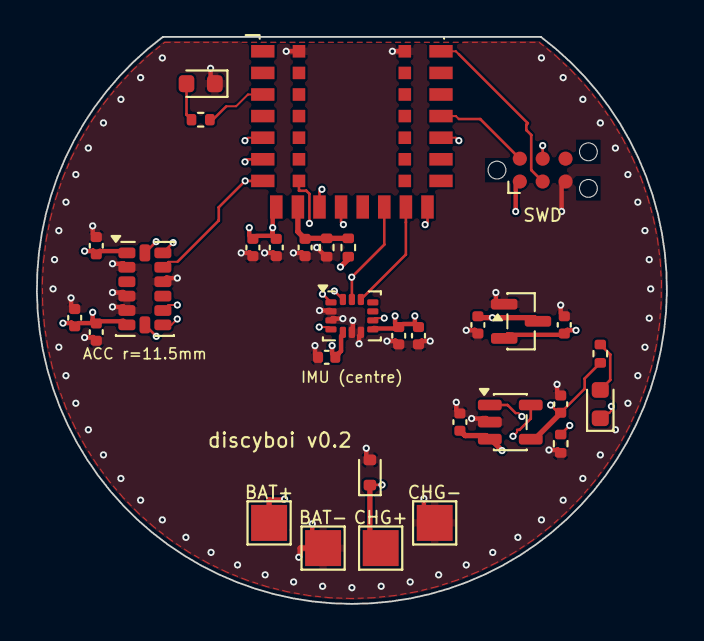
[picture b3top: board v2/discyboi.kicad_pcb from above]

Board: 4 copper layers, 35.0 x 31.5 mm, 31 parts (0 on the bottom side), 22 nets.

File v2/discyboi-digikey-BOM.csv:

Quantity,Manufacturer,Manufacturer Part Number,Reference Designators,Value,Footprint
2,Samsung,CL05A106MQ5NUNC,C1 C21,10u,C_0402_1005Metric
6,Samsung,CL05B104KO5NNNC,C2 C10 C12 C18 C19 C20,100n,C_0402_1005Metric
3,Samsung,CL05A105KA5NQNC,C11 C16 C17,1u,C_0402_1005Metric
2,Samsung,CL05A475MP5NRNC,C13 C14,4.7u,C_0402_1005Metric
1,Lite-On,LTST-C191KGKT,D1,Green,LED_0603_1608Metric
1,Lite-On,LTST-C191KRKT,D2,Red,LED_0603_1608Metric
1,onsemi,ESD5Z5.0T1G,D3,ESD5Z5.0T1G,D_SOD-523
2,Yageo,RC0402FR-071ML,R3 R4,1M,R_0402_1005Metric
2,Yageo,RC0402FR-071KL,R5 R8,1k,R_0402_1005Metric
1,Yageo,RC0402FR-0710KL,R7,10k,R_0402_1005Metric
1,Microchip,MCP1700T-3002E/TT,U2,MCP1700T-3002E/TT,SOT-23
1,Analog Devices,ADXL375BCCZ-RL7,U3,ADXL375BCCZ,LGA-14_3x5mm_P0.8mm_LayoutBorder1x6y
1,Microchip,MCP73831T-2ACI/OT,U4,MCP73831T-2ACI/OT,SOT-23-5
1,STMicroelectronics,LSM6DSV16XTR,U5,LSM6DSV16XTR,LGA-14_3x2.5mm_P0.5mm_LayoutBorder3x4y

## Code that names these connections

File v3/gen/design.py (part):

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    'D1': 'ACC_INT2',   # P1.12
    'B6': 'VBAT_SENSE', # P1.06 / AIN2
    'A5': 'LED',        # P2.09
    'F4': 'CHG_DET',    # P1.03 (NFC2 pad, used as GPIO): high = charger connected, wake source
}

ICM_PINS = {  # LSM6DSV320X (DS14623 rev 3, table 2; same pinout as LSM6DSV16X) - SPI 4-wire, aux/Qvar unused
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    cap('C21', '1u', '+3V0', 'GND'),
    cap('C20', '100n', '+3V0', 'GND'),
    # ---------------- power: charge pads -> MCP73831 -> LiPo pads -> MCP1700 3.0V
    dict(ref='TP3', lib='Connector:TestPoint', value='CHG+ (5V)', fp='TestPoint:TestPoint_Pad_2.0x2.0mm', pins={'1': 'VCHG'}, in_bom=False),
    dict(ref='TP4', lib='Connector:TestPoint', value='CHG-', fp='TestPoint:TestPoint_Pad_2.0x2.0mm', pins={'1': 'GND'}, in_bom=False),
    dict(ref='TP1', lib='Connector:TestPoint', value='BAT+', fp='TestPoint:TestPoint_Pad_2.0x2.0mm', pins={'1': 'VBAT'}, in_bom=False),
    dict(ref='TP2', lib='Connector:TestPoint', value='BAT-', fp='TestPoint:TestPoint_Pad_2.0x2.0mm', pins={'1': 'GND'}, in_bom=False),
    dict(ref='D3', lib='Device:D_Zener_Small', value='ESD5Z5.0T1G', fp='Diode_SMD:D_SOD-523',
         pins={'1': 'VCHG', '2': 'GND'}, mfr='onsemi', mpn='ESD5Z5.0T1G', lcsc='C82044'),
    cap('C13', '4.7u', 'VCHG', 'GND'),
    dict(ref='U4', lib='Battery_Management:MCP73831-2-OT', value='MCP73831T-2ACI/OT', fp='Package_TO_SOT_SMD:SOT-23-5',
         pins={'1': 'CHG_STAT', '2': 'GND', '3': 'VBAT', '4': 'VCHG', '5': 'PROG'}, mfr='Microchip', mpn='MCP73831T-2ACI/OT', lcsc='C424093'),
    res('R7', '10k', 'PROG', 'GND'),          # 1000V/10k = 100 mA charge current
    cap('C14', '4.7u', 'VBAT', 'GND'),
    res('R8', '1k', 'VCHG', 'CHG_LED'),
    dict(ref='D2', lib='Device:LED_Small', value='Red', fp='LED_SMD:LED_0603_1608Metric',
         pins={'1': 'CHG_STAT', '2': 'CHG_LED'}, mfr='Lite-On', mpn='LTST-C191KRKT', lcsc='C2286'),
    dict(ref='U2', lib='Regulator_Linear:MCP1700x-300xxTT', value='MCP1700T-3002E/TT', fp='Package_TO_SOT_SMD:SOT-23',
         pins={'1': 'GND', '2': '+3V0', '3': 'VBAT'}, mfr='Microchip', mpn='MCP1700T-3002E/TT', lcsc='C62244'),
    cap('C16', '1u', 'VBAT', 'GND'),
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    # ---------------- debug + status LED
    dict(ref='J2', lib='Connector:Conn_ARM_SWD_TagConnect_TC2030', value='TC2030-IDC-NL',
         fp='Connector:Tag-Connect_TC2030-IDC-NL_2x03_P1.27mm_Vertical',
         pins={'1': '+3V0', '2': 'SWDIO', '3': 'NRESET', '4': 'SWDCLK', '5': 'GND', '6': None}, in_bom=False),
    res('R5', '1k', 'LED', 'LED_A'),
    dict(ref='D1', lib='Device:LED_Small', value='Green', fp='LED_SMD:LED_0603_1608Metric',
         pins={'1': 'GND', '2': 'LED_A'}, mfr='Lite-On', mpn='LTST-C191KGKT', lcsc='C72043'),
]

PWR_FLAGS = ['GND', 'VCHG']
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    y = 22.86
    for k in left:
        if k:
            et = {'VDD': 'power_in', 'GND': 'power_in', 'SWDCLK': 'input', 'SWDIO': 'bidirectional', 'NRESET': 'bidirectional'}[MOD_PINS[k]]
            pins.append(pin(et, -17.78, y, 0, MOD_PINS[k], k))
        y -= 2.54
    y = 22.86
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

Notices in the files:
v4/README.md:
The v4 hardware (schematic, PCB, generators in `gen/`, fabrication files in `jlcpcb/` and the enclosure in `enclosure/`) is licensed under the [CERN Open Hardware Licence v2, strongly reciprocal](../LICENSES/CERN-OHL-S-2.0.txt) (CERN-OHL-S-2.0). See [LICENSE.md](../LICENSE.md).
Source location: https://github.com/hrafnkell/discyboi
